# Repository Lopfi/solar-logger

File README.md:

# Solar Logger

This is a simple box with an ESP32 with a LC12S, build to replace a DataBox24G from All of Solar, which communicates with a solar inverter to collect data on power generation.

All configuration is in `/firmware/include/config-example.h` just change the values to your needs and rename it to `config.h`.

For more information on how the hardware works and how I did the reverse engineering visit the hackaday project [here](https://hackaday.io/project/186606-solar-inverter-datalogger-improvements).

If anyone is interested in a the PCB with LC12S and ESP32 for easy communication with the panel and integration into any smarthome system feel free to contact me.

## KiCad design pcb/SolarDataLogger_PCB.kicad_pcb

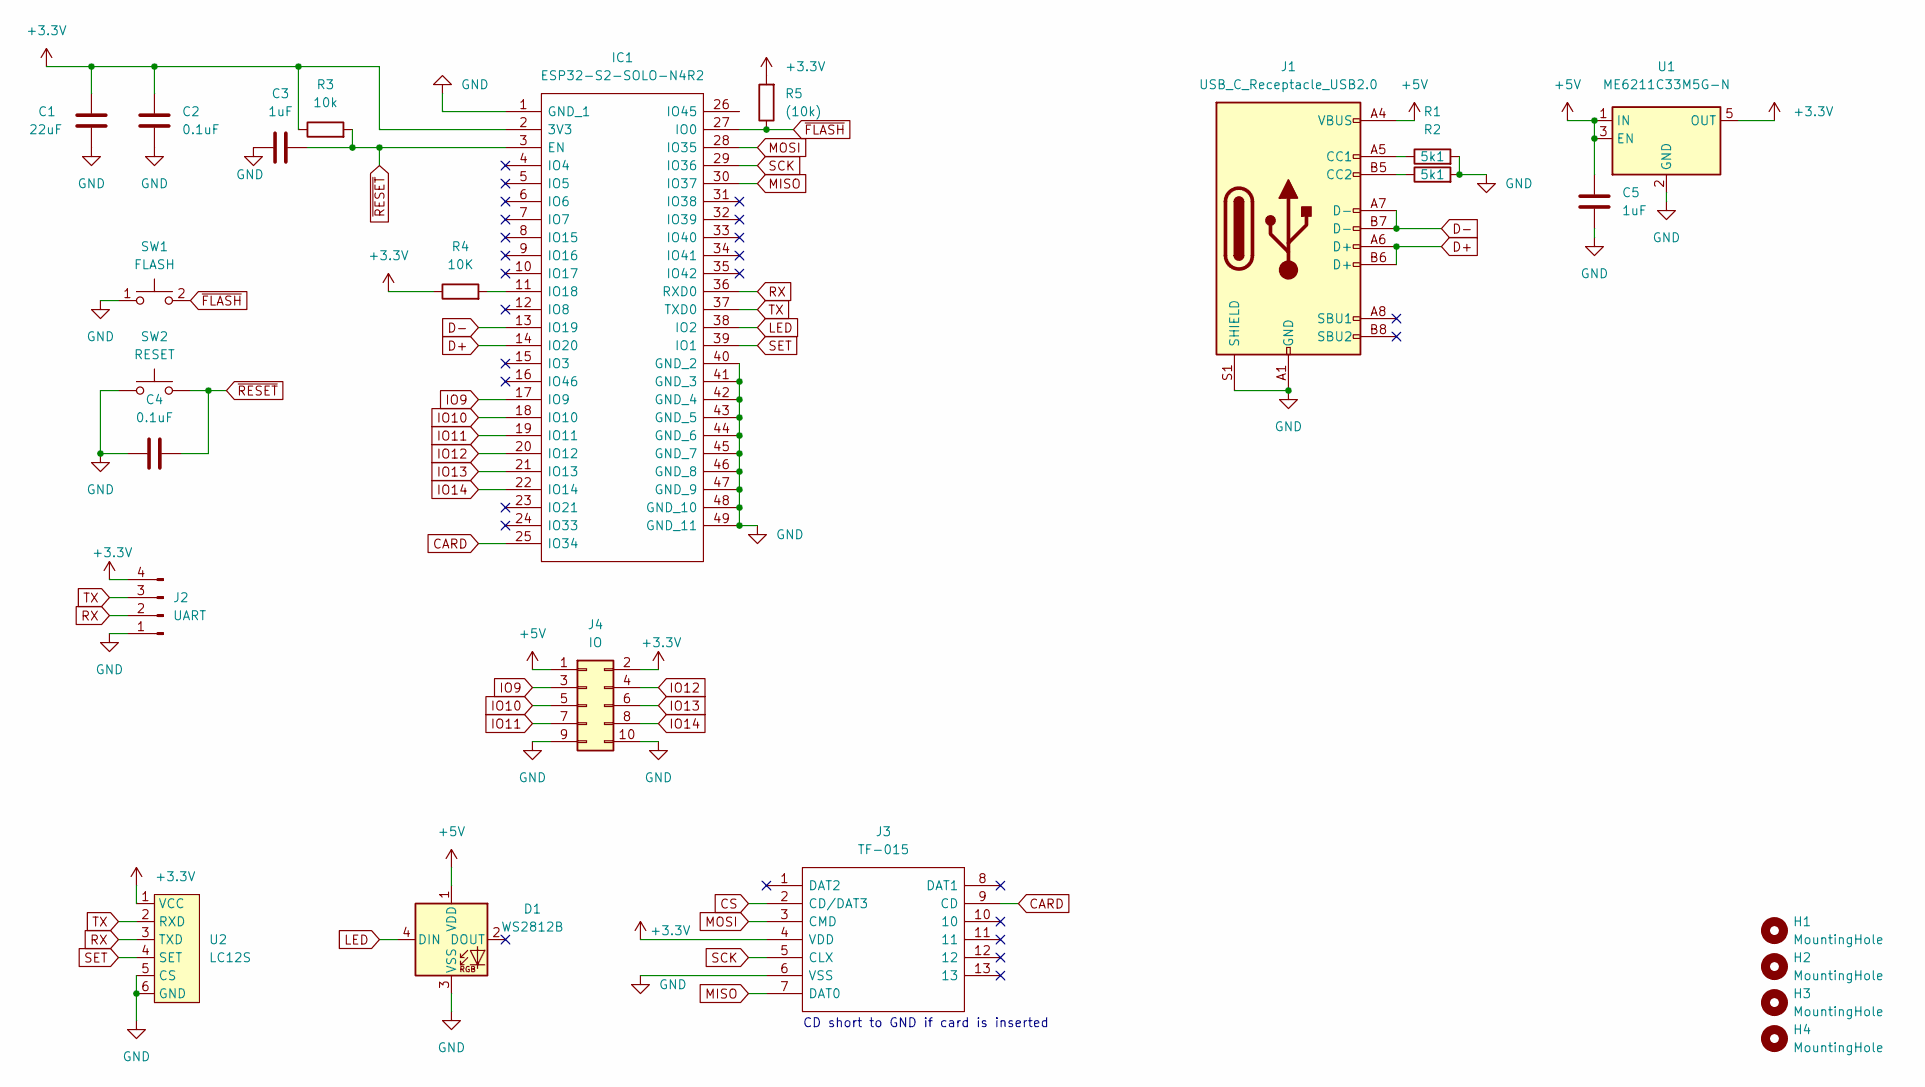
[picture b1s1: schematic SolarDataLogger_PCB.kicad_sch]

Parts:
C1: 22uF; C_0805_2012Metric_Pad1.18x1.45mm_HandSolder
C2, C4: 0.1uF; C_0805_2012Metric_Pad1.18x1.45mm_HandSolder
C3, C5: 1uF; C_0805_2012Metric_Pad1.18x1.45mm_HandSolder
D1: WS2812B; LED_WS2812B_PLCC4_5.0x5.0mm_P3.2mm
H1, H2, H3, H4: MountingHole; MountingHole_2.2mm_M2
IC1: ESP32-S2-SOLO-N4R2; ESP32S2SOLON4R2; Manufacturer_Part_Number ESP32-S2-SOLO-N4R2; Mouser Part Number 356-ESP32-S2SOLON4R2
J1: USB_C_Receptacle_USB2.0; USB_C_Receptacle_HRO_TYPE-C-31-M-12
J2: UART; PinHeader_1x04_P2.54mm_Vertical
J3: TF-015; TF015; Manufacturer_Part_Number TF-015
J4: IO; PinHeader_2x05_P2.54mm_Vertical
R1, R2: 5k1; R_0805_2012Metric_Pad1.20x1.40mm_HandSolder
R3: 10k; R_0805_2012Metric_Pad1.20x1.40mm_HandSolder
R4: 10K; R_0805_2012Metric_Pad1.20x1.40mm_HandSolder
R5: (10k); R_0805_2012Metric_Pad1.20x1.40mm_HandSolder
SW1: FLASH; TS1187ABAB
SW2: RESET; TS1187ABAB
U1: ME6211C33M5G-N; SOT-23-5_HandSoldering
U2: LC12S

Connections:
+3.3V: C1.2, C2.2, IC1.2 (3V3), J2.4, J3.4 (VDD), J4.2, R3.1, R4.1, R5.2, U1.5 (OUT), U2.1 (VCC)
+5V: C5.1, D1.1 (VDD), J1.A4 (VBUS), J1.A9 (VBUS), J1.B4 (VBUS), J1.B9 (VBUS), J4.1, U1.1 (IN), U1.3 (EN)
CARD: IC1.25 (IO34), J3.9 (CD)
CS: J3.2 (CD/DAT3)
D+: IC1.14 (IO20), J1.A6 (D+), J1.B6 (D+)
D-: IC1.13 (IO19), J1.A7 (D-), J1.B7 (D-)
GND: C1.1, C2.1, C3.1, C4.2, C5.2, D1.3 (VSS), IC1.1 (GND_1), IC1.40 (GND_2), IC1.41 (GND_3), IC1.42 (GND_4), IC1.43 (GND_5), IC1.44 (GND_6), IC1.45 (GND_7), IC1.46 (GND_8), IC1.47 (GND_9), IC1.48 (GND_10), IC1.49 (GND_11), J1.A1 (GND), J1.A12 (GND), J1.B1 (GND), J1.B12 (GND), J1.S1 (SHIELD), J2.1, J3.6 (VSS), J4.9, J4.10, R1.2, R2.2, SW1.1, SW2.1, U1.2 (GND), U2.5 (CS), U2.6 (GND)
IO9: IC1.17 (IO9), J4.3
IO10: IC1.18 (IO10), J4.5
IO11: IC1.19 (IO11), J4.7
IO12: IC1.20 (IO12), J4.4
IO13: IC1.21 (IO13), J4.6
IO14: IC1.22 (IO14), J4.8
LED: D1.4 (DIN), IC1.38 (IO2)
MISO: IC1.30 (IO37), J3.7 (DAT0)
MOSI: IC1.28 (IO35), J3.3 (CMD)
unnamed: IC1.11 (IO18), R4.2
unnamed: J1.A5 (CC1), R1.1
unnamed: J1.B5 (CC2), R2.1
RX: IC1.36 (RXD0), J2.2, U2.3 (TXD)
SCK: IC1.29 (IO36), J3.5 (CLX)
SET: IC1.39 (IO1), U2.4 (SET)
TX: IC1.37 (TXD0), J2.3, U2.2 (RXD)
~FLASH: IC1.27 (IO0), R5.1, SW1.2
~RESET: C3.2, C4.1, IC1.3 (EN), R3.2, SW2.2

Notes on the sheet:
CD short to GND if card is inserted

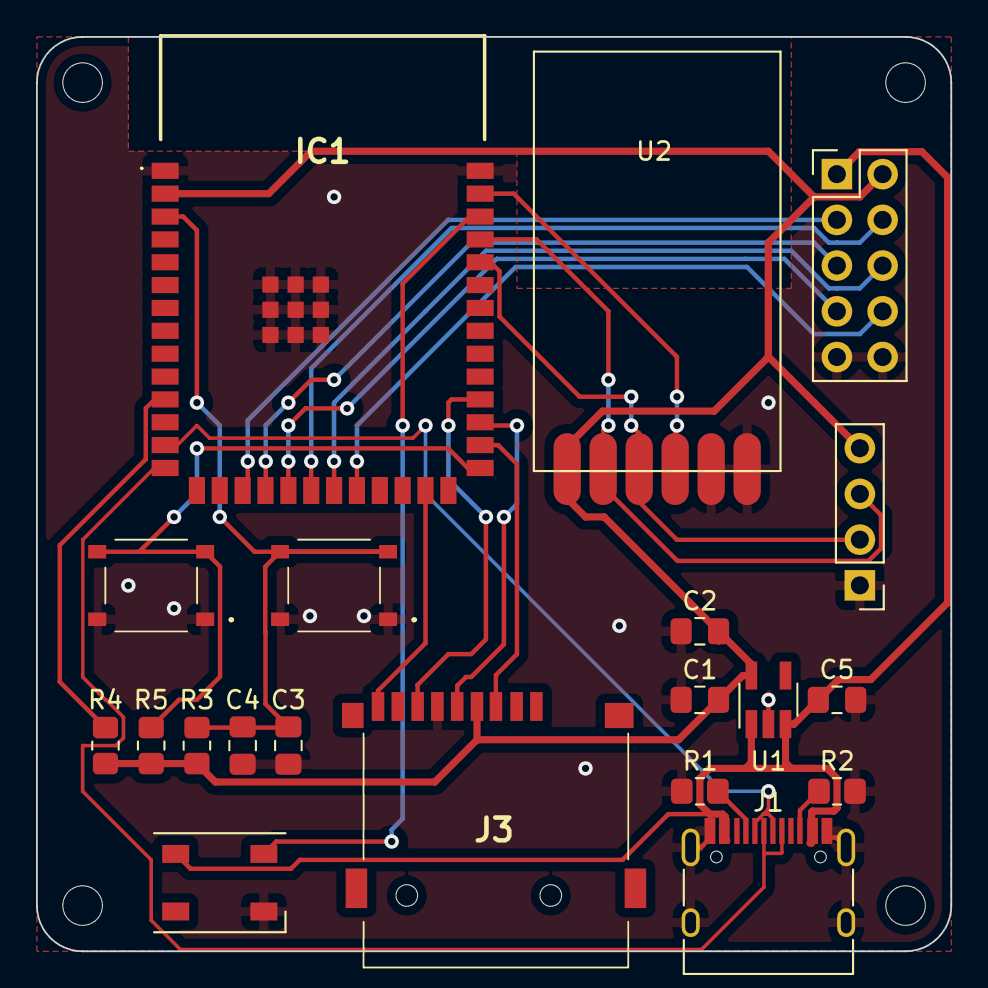
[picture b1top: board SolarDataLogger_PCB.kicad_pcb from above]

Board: 2 copper layers, 50.8 x 50.8 mm, 24 parts (0 on the bottom side), 24 nets.

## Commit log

2022-10-17 add config-example.h
2022-10-17 update gitignore
2022-10-24 add check for inverter and box id and timeout
2022-10-26 minor changes
2022-11-03 add clear fields
2023-01-27 add esp32s2 board
2024-07-06 add led
2024-07-06 fix pins and serial
2024-07-06 add pcb and casse
2024-07-06 open project
2024-07-06 add vscode folder to gitignore
2024-07-13 fix gitignore
2024-07-16 show led status first
2024-08-17 fix config
2024-08-17 switch to NETSGPClient library
2024-09-27 Change total_gen to float
